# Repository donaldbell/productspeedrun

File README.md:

# Product Speedrun

**Product Speedrun** is a show about racing a randomly rolled product idea to a showcase-ready concept: an enclosure design, a circuit board and a product page. Everything the show designs is open, and this repository holds it.

**See the products:** https://donaldbell.github.io/productspeedrun/

Every product here is a **design proposal**, not something you can buy. Nothing has been manufactured, and each page lists what we still don't know.

## What's here

```
episodes/<NNN-slug>/        one folder per episode (Rev A, as aired)
  2-concept/, 3-layout/     concept art and control drawings
  4-model/                  the enclosure: model.step, model.stl, model.glb, notes
  5-electronics/            the circuit board: KiCad project, bom.csv, schematic and board renders, notes
  6-showcase/               the product page
products/<product>/rev-b/   later revisions of products we kept building, including firmware (7-firmware/)
tools/kicad/footprints/     custom footprints the KiCad projects use
tools/kicad/models/         3D models of parts the KiCad projects use
kit/                        the shared look of the product pages
```

## Using the designs

- **Enclosures:** open `4-model/model.step` in any CAD program, or print from `model.stl`. `build_model.py` and `model.solidcraft` are kept as a record of how the model was made; edit the STEP file.
- **Circuit boards:** open the `.kicad_pro` in [KiCad](https://www.kicad.org/) (the version each board was saved with is on its page). Keep the repository's folder layout so the custom footprints and 3D models in `tools/kicad/` are found. `src/design.py` and `src/layout.py` record the parts, nets and placement the board was generated from; edit the KiCad files.
- **Firmware:** PlatformIO projects in `products/<product>/rev-*/7-firmware/`.
- Each product page has a **Build on it** section with direct downloads and a prompt that hands the project to an AI coding agent.

## Licence and credit

Hardware is under CERN-OHL-P v2, writing and images under CC BY 4.0, and code under MIT. Details are in [LICENSE](LICENSE), the full texts in [LICENSES/](LICENSES/), and who made each episode in [CREDITS.md](CREDITS.md).

Credit line for reuse: *Based on Product Speedrun episode NNN by Donald Bell and &lt;guest&gt;, https://donaldbell.github.io/productspeedrun/*

The name "Product Speedrun" and its logo aren't covered by these licences.

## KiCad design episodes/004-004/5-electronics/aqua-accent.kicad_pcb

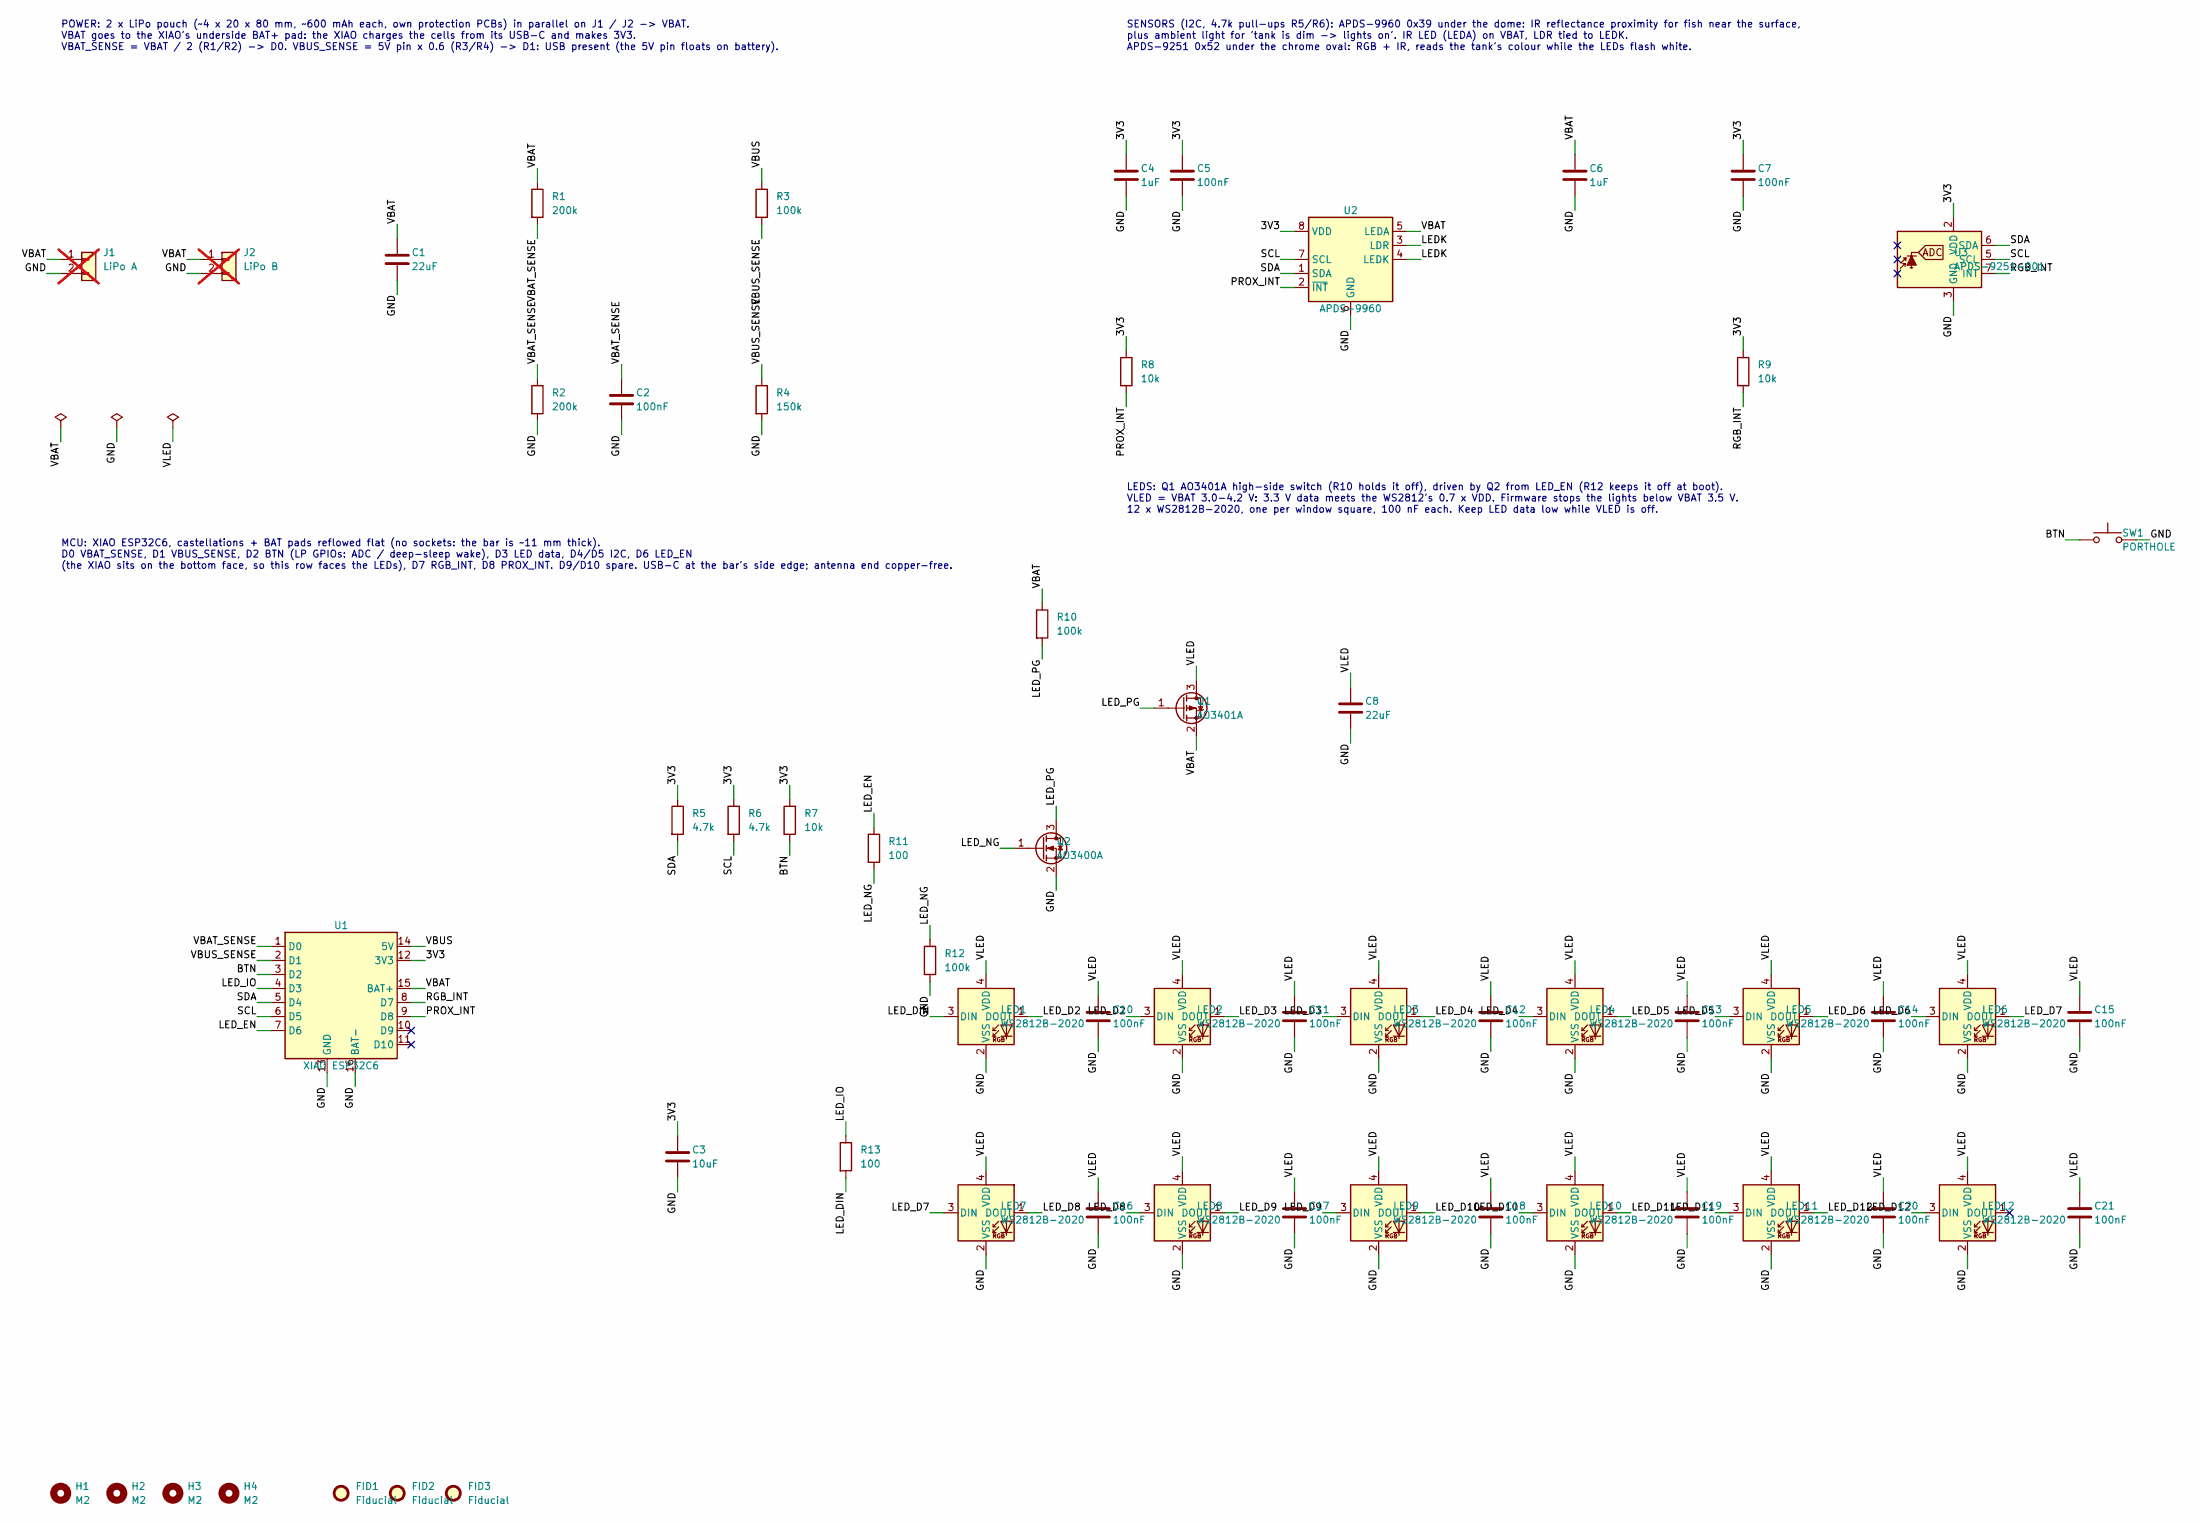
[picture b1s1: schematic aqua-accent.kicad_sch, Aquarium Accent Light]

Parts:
C1, C8: 22uF; C_0805_2012Metric; MPN CL21A226MAQNNNE; LCSC C45783
C2, C5, C7, C10, C11, C12, C13, C14, C15, C16, C17, C18, C19, C20, C21: 100nF; C_0603_1608Metric; MPN CC0603KRX7R9BB104; LCSC C14663
C3: 10uF; C_0805_2012Metric; MPN CL21A106KAYNNNE; LCSC C15850
C4, C6: 1uF; C_0603_1608Metric; MPN CL10A105KB8NNNC; LCSC C15849
FID1, FID2, FID3: Fiducial; Fiducial_1mm_Mask2mm
H1, H2, H3, H4: M2; MountingHole_2.2mm_M2
J1: LiPo A; SolderWire-0.1sqmm_1x02_P3.6mm_D0.4mm_OD1mm; not fitted
J2: LiPo B; SolderWire-0.1sqmm_1x02_P3.6mm_D0.4mm_OD1mm; not fitted
LED1, LED2, LED3, LED4, LED5, LED6, LED7, LED8, LED9, LED10, LED11, LED12: WS2812B-2020; LED_WS2812B-2020_PLCC4_2.0x2.0mm; MPN WS2812B-2020; LCSC C965555
Q1: AO3401A; SOT-23; MPN AO3401A; LCSC C15127
Q2: AO3400A; SOT-23; MPN AO3400A; LCSC C20917
R1, R2: 200k; R_0603_1608Metric; MPN 0603WAF2003T5E; LCSC C25811
R3, R10, R12: 100k; R_0603_1608Metric; MPN 0603WAF1003T5E; LCSC C25803
R4: 150k; R_0603_1608Metric; MPN 0603WAF1503T5E; LCSC C22807
R5, R6: 4.7k; R_0603_1608Metric; MPN 0603WAF4701T5E; LCSC C23162
R7, R8, R9: 10k; R_0603_1608Metric; MPN 0603WAF1002T5E; LCSC C25804
R11, R13: 100; R_0603_1608Metric; MPN 0603WAF1000T5E; LCSC C22775
SW1: PORTHOLE; SW_SPST_PTS810; MPN PTS810 SJM 250 SMTR LFS
U1: XIAO ESP32C6; Seeed_XIAO_ESP32C6_SMD; MPN 113991254
U2: APDS-9960; Avago_APDS-9960; MPN APDS-9960
U3: APDS-9251-001; Broadcom_LGA-8_2x2mm_P0.5mm; MPN APDS-9251-001

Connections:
/3V3: C3.1, C4.1, C5.1, C7.1, R5.1, R6.1, R7.1, R8.1, R9.1, U1.12 (3V3), U2.8 (VDD), U3.2 (VDD)
/BTN: R7.2, SW1.1, U1.3 (D2)
/GND: C1.2, C2.2, C3.2, C4.2, C5.2, C6.2, C7.2, C8.2, C10.2, C11.2, C12.2, C13.2, C14.2, C15.2, C16.2, C17.2, C18.2, C19.2, C20.2, C21.2, J1.2, J2.2, LED1.2 (VSS), LED2.2 (VSS), LED3.2 (VSS), LED4.2 (VSS), LED5.2 (VSS), LED6.2 (VSS), LED7.2 (VSS), LED8.2 (VSS), LED9.2 (VSS), LED10.2 (VSS), LED11.2 (VSS), LED12.2 (VSS), Q2.2 (S), R2.2, R4.2, R12.2, SW1.2, U1.13 (GND), U1.16 (BAT-), U2.6 (GND), U3.3 (GND)
/LEDK: U2.3 (LDR), U2.4 (LEDK)
/LED_D2: LED1.1 (DOUT), LED2.3 (DIN)
/LED_D3: LED2.1 (DOUT), LED3.3 (DIN)
/LED_D4: LED3.1 (DOUT), LED4.3 (DIN)
/LED_D5: LED4.1 (DOUT), LED5.3 (DIN)
/LED_D6: LED5.1 (DOUT), LED6.3 (DIN)
/LED_D7: LED6.1 (DOUT), LED7.3 (DIN)
/LED_D8: LED7.1 (DOUT), LED8.3 (DIN)
/LED_D9: LED8.1 (DOUT), LED9.3 (DIN)
/LED_D10: LED9.1 (DOUT), LED10.3 (DIN)
/LED_D11: LED10.1 (DOUT), LED11.3 (DIN)
/LED_D12: LED11.1 (DOUT), LED12.3 (DIN)
/LED_DIN: LED1.3 (DIN), R13.2
/LED_EN: R11.1, U1.7 (D6)
/LED_IO: R13.1, U1.4 (D3)
/LED_NG: Q2.1 (G), R11.2, R12.1
/LED_PG: Q1.1 (G), Q2.3 (D), R10.2
/PROX_INT: R8.2, U1.9 (D8), U2.2 (~INT)
/RGB_INT: R9.2, U1.8 (D7), U3.7 (INT)
/SCL: R6.2, U1.6 (D5), U2.7 (SCL), U3.5 (SCL)
/SDA: R5.2, U1.5 (D4), U2.1 (SDA), U3.6 (SDA)
/VBAT: C1.1, C6.1, J1.1, J2.1, Q1.2 (S), R1.1, R10.1, U1.15 (BAT+), U2.5 (LEDA)
/VBAT_SENSE: C2.1, R1.2, R2.1, U1.1 (D0)
/VBUS: R3.1, U1.14 (5V)
/VBUS_SENSE: R3.2, R4.1, U1.2 (D1)
/VLED: C8.1, C10.1, C11.1, C12.1, C13.1, C14.1, C15.1, C16.1, C17.1, C18.1, C19.1, C20.1, C21.1, LED1.4 (VDD), LED2.4 (VDD), LED3.4 (VDD), LED4.4 (VDD), LED5.4 (VDD), LED6.4 (VDD), LED7.4 (VDD), LED8.4 (VDD), LED9.4 (VDD), LED10.4 (VDD), LED11.4 (VDD), LED12.4 (VDD), Q1.3 (D)

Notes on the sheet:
POWER: 2 x LiPo pouch (~4 x 20 x 80 mm, ~600 mAh each, own protection PCBs) in parallel on J1 / J2 -> VBAT. VBAT goes to the XIAO's underside BAT+ pad: the XIAO charges the cells from its USB-C and makes 3V3. VBAT_SENSE = VBAT / 2 (R1/R2) -> D0. VBUS_SENSE = 5V pin x 0.6 (R3/R4) -> D1: USB present 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
MCU: XIAO ESP32C6, castellations + BAT pads reflowed flat (no sockets: the bar is ~11 mm thick). D0 VBAT_SENSE, D1 VBUS_SENSE, D2 BTN (LP GPIOs: ADC / deep-sleep wake), D3 LED data, D4/D5 I2C, D6 LED_EN (the XIAO sits on the bottom face, so this row faces the LEDs), D7 RGB_INT, D8 PROX_INT. D9/D10 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
SENSORS (I2C, 4.7k pull-ups R5/R6): APDS-9960 0x39 under the dome: IR reflectance proximity for fish near the surface, plus ambient light for 'tank is dim -> lights on'. IR LED (LEDA) on VBAT, LDR tied to LEDK. APDS-9251 0x52 under the chrome oval: RGB + IR, reads the tank's colour while the LEDs f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
LEDS: Q1 AO3401A high-side switch (R10 holds it off), driven by Q2 from LED_EN (R12 keeps it off at boot). VLED = VBAT 3.0-4.2 V: 3.3 V data meets the WS2812's 0.7 x VDD. Firmware stops the lights below VBAT 3.5 V. 12 x WS2812B-2020, one per window square, 100 nF each. Keep LED data low while VLED 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

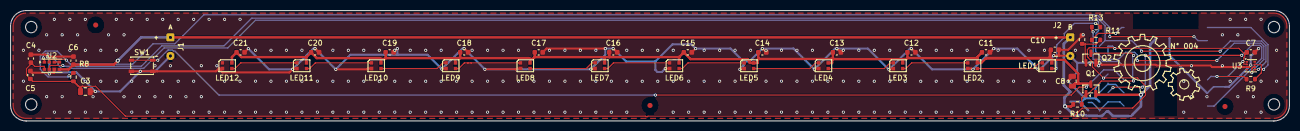
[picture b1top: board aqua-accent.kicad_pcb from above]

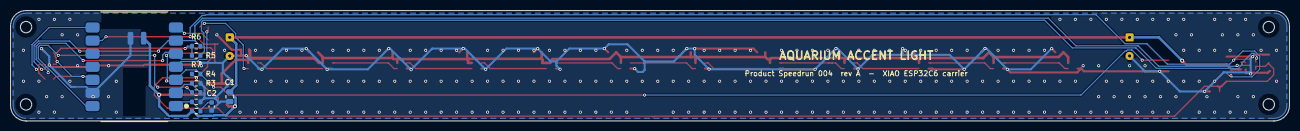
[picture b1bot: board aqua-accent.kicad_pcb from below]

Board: 2 copper layers, 248.0 x 21.4 mm, 60 parts (10 on the bottom side), 29 nets.

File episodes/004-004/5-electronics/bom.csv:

Ref,Qty,Value,Description,Footprint,MPN
C1 C8,2,22uF,"Capacitor, ceramic, 22 uF 25 V X5R 0805",C_0805_2012Metric,CL21A226MAQNNNE
C2 C5 C7 C10 C11 C12 C13 C14 C15 C16 C17 C18 C19 C20 C21,15,100nF,"Capacitor, ceramic, 100 nF 50 V X7R 0603",C_0603_1608Metric,CC0603KRX7R9BB104
C3,1,10uF,"Capacitor, ceramic, 10 uF 25 V X5R 0805",C_0805_2012Metric,CL21A106KAYNNNE
C4 C6,2,1uF,"Capacitor, ceramic, 1 uF 50 V X5R 0603",C_0603_1608Metric,CL10A105KB8NNNC
LED1 LED2 LED3 LED4 LED5 LED6 LED7 LED8 LED9 LED10 LED11 LED12,12,WS2812B-2020,"RGB LED 2 x 2 mm, one under each of the 12 window squares",LED_WS2812B-2020_PLCC4_2.0x2.0mm,WS2812B-2020
Q1,1,AO3401A,P-MOSFET -30 V -4 A SOT-23: high-side switch for the LED chain,SOT-23,AO3401A
Q2,1,AO3400A,N-MOSFET 30 V 5.7 A SOT-23: drives Q1's gate from the 3.3 V GPIO,SOT-23,AO3400A
R1 R2,2,200k,"Resistor, 1 %, 0603, 200k",R_0603_1608Metric,0603WAF2003T5E
R3 R10 R12,3,100k,"Resistor, 1 %, 0603, 100k",R_0603_1608Metric,0603WAF1003T5E
R4,1,150k,"Resistor, 1 %, 0603, 150k",R_0603_1608Metric,0603WAF1503T5E
R5 R6,2,4.7k,"Resistor, 1 %, 0603, 4.7k",R_0603_1608Metric,0603WAF4701T5E
R7 R8 R9,3,10k,"Resistor, 1 %, 0603, 10k",R_0603_1608Metric,0603WAF1002T5E
R11 R13,2,100,"Resistor, 1 %, 0603, 100",R_0603_1608Metric,0603WAF1000T5E
SW1,1,PORTHOLE,"Tact switch 4.2 x 3.2 x 2.5 mm SMD under the porthole boss: wake, mode, hold = open the control panel",SW_SPST_PTS810,PTS810 SJM 250 SMTR LFS
U1,1,XIAO ESP32C6,"Seeed XIAO ESP32C6 (USB-C, LiPo charger, 3.3 V LDO, ceramic antenna), castellations + BAT pads reflowed to the carrier",Seeed_XIAO_ESP32C6_SMD,113991254
U2,1,APDS-9960,"Proximity / gesture / ambient / RGBC sensor with IR LED, I2C 0x39: fish near the surface, room light",Avago_APDS-9960,APDS-9960
U3,1,APDS-9251-001,"Digital RGB + IR light sensor, I2C 0x52: reads the tank's colour",Broadcom_LGA-8_2x2mm_P0.5mm,APDS-9251-001
BT1,1,LiPo ~600 mAh,"LiPo pouch 3.7 V ~600 mAh, ~4 x 20 x 80 mm, with protection PCB, leads soldered to J1",off-board,generic 402080
BT2,1,LiPo ~600 mAh,"Second, matching cell in parallel, leads soldered to J2 (charge both to the same voltage before joining)",off-board,generic 402080

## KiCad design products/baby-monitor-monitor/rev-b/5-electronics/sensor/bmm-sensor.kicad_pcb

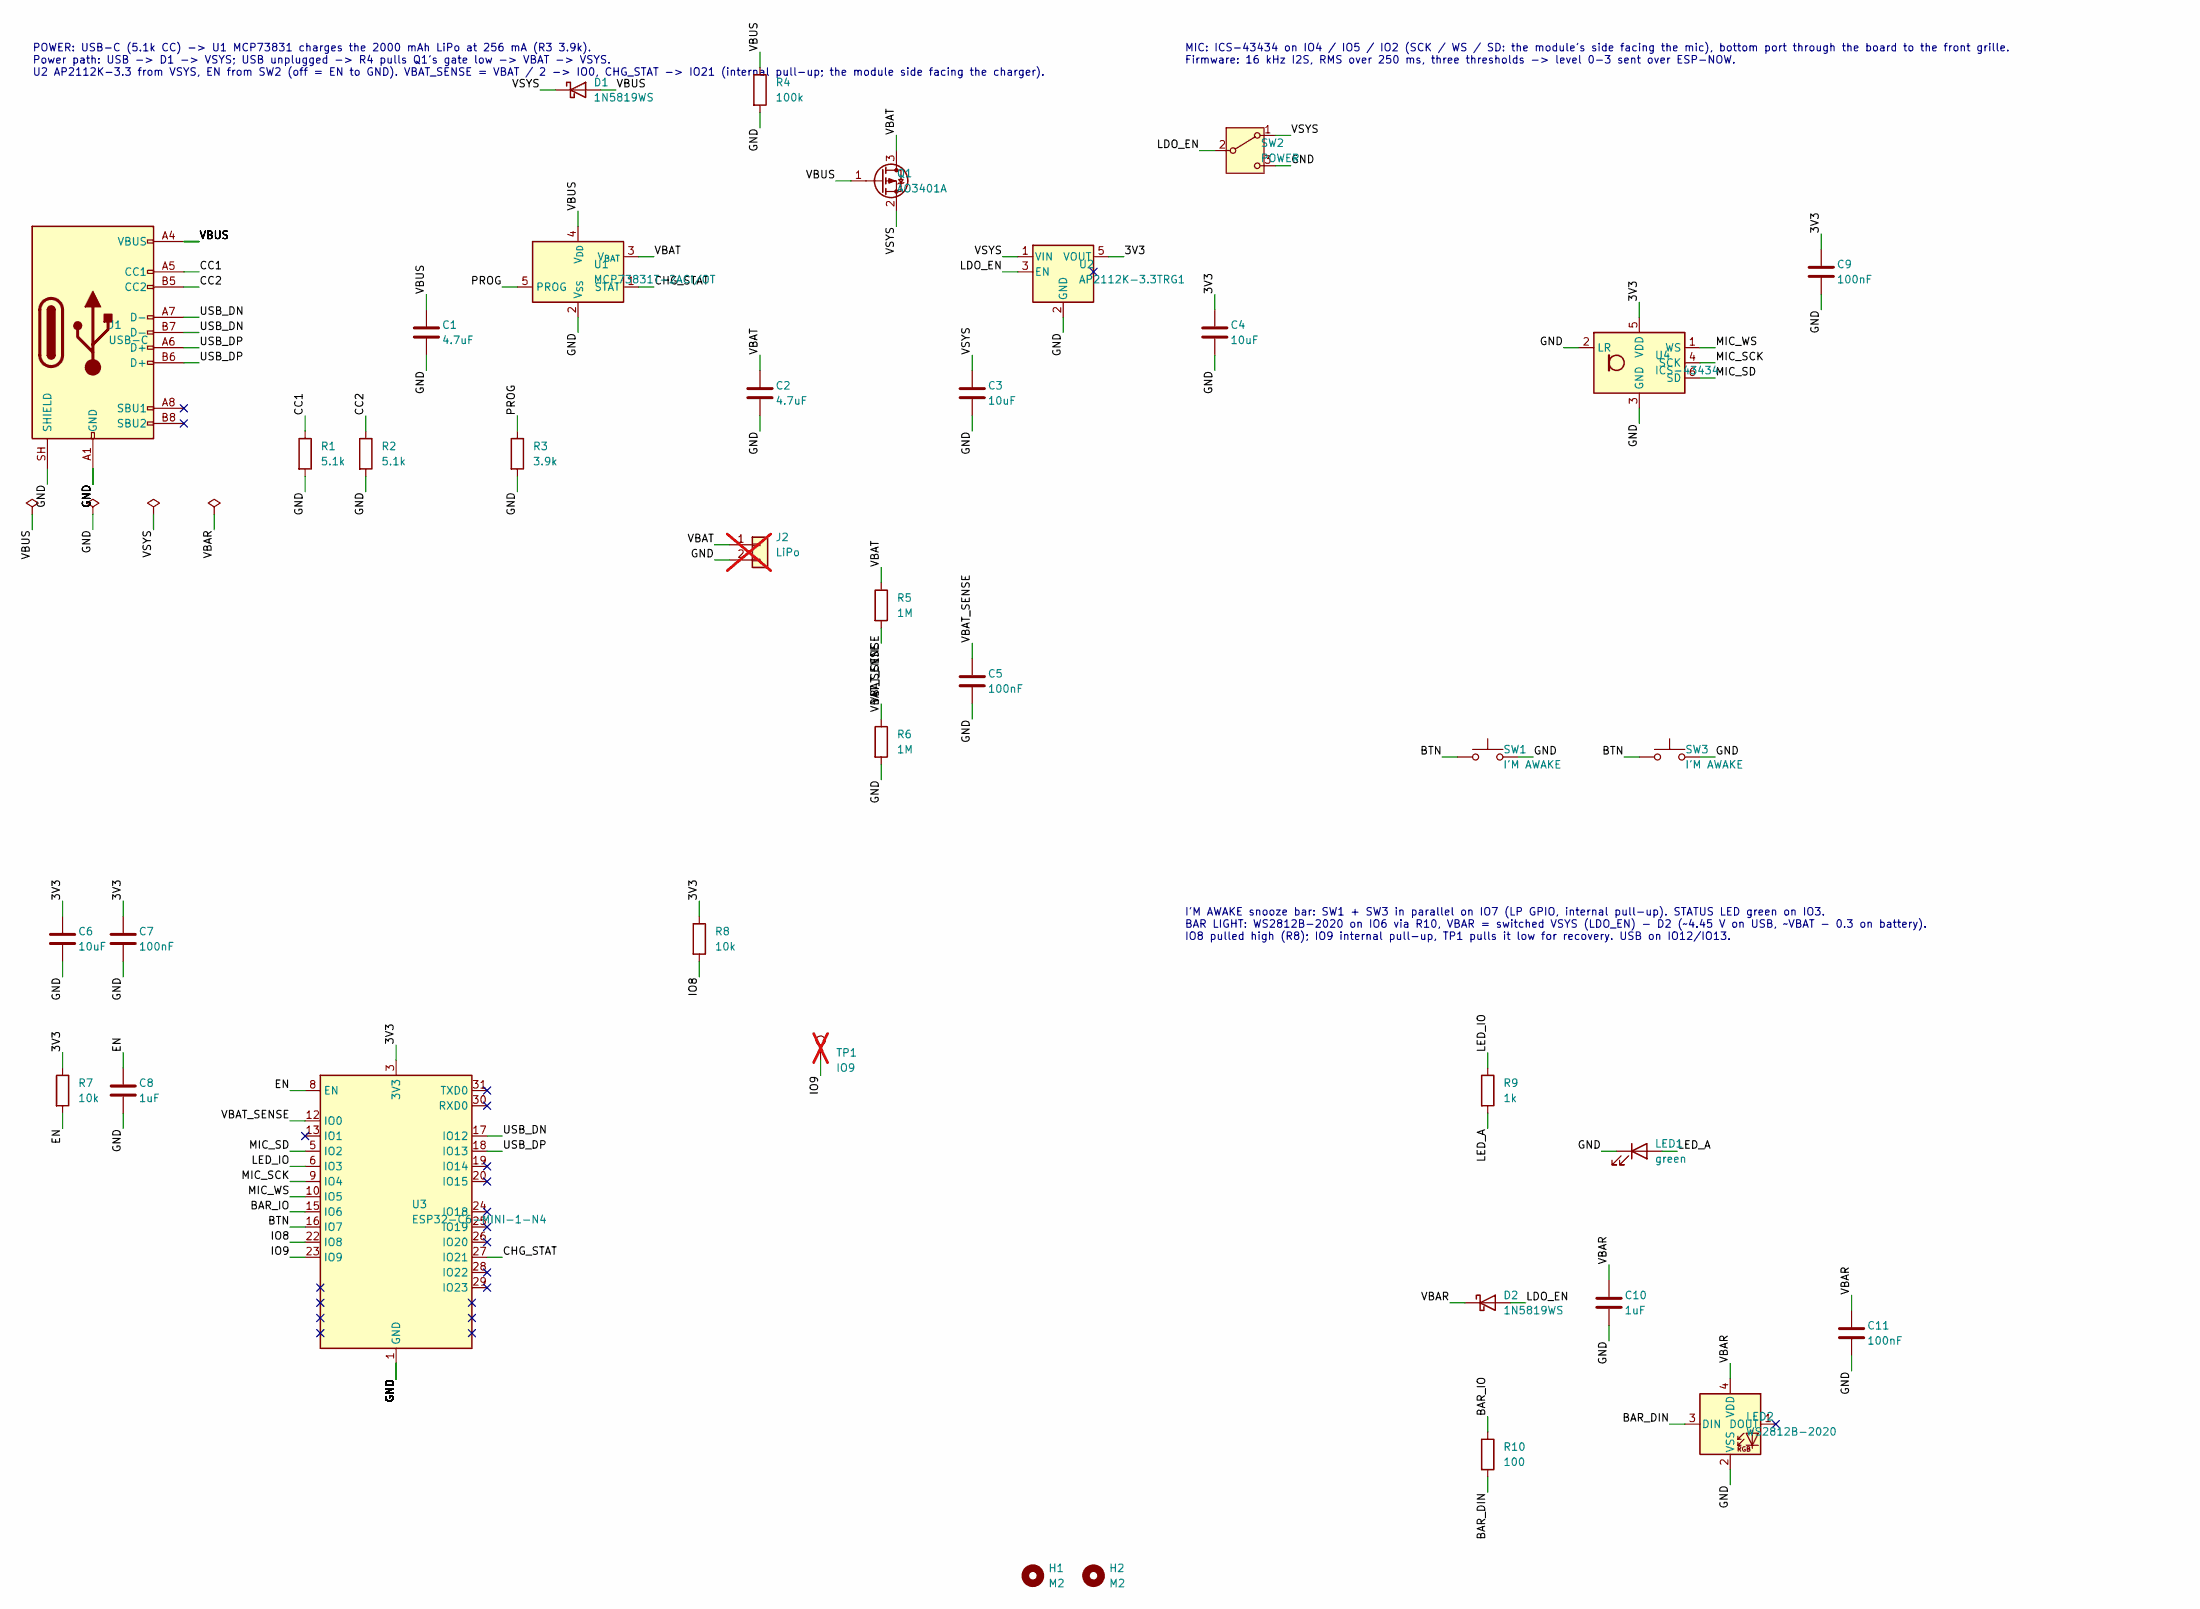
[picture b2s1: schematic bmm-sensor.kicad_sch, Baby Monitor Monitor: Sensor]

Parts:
C1, C2: 4.7uF; C_0603_1608Metric; MPN CL10A475KO8NNNC; LCSC C19666
C3, C4, C6: 10uF; C_0805_2012Metric; MPN CL21A106KAYNNNE; LCSC C15850
C5, C7, C9, C11: 100nF; C_0603_1608Metric; MPN CC0603KRX7R9BB104; LCSC C14663
C8, C10: 1uF; C_0603_1608Metric; MPN CL10A105KB8NNNC; LCSC C15849
D1, D2: 1N5819WS; D_SOD-323; MPN 1N5819WS; LCSC C191023
H1, H2: M2; MountingHole_2.2mm_M2
J1: USB-C; USB_C_Receptacle_GCT_USB4105-xx-A_16P_TopMnt_Horizontal; MPN USB4105-GF-A
J2: LiPo; SolderWire-0.1sqmm_1x02_P3.6mm_D0.4mm_OD1mm; not fitted
LED1: green; LED_0603_1608Metric; MPN KT-0603G; LCSC C72043
LED2: WS2812B-2020; LED_WS2812B-2020_PLCC4_2.0x2.0mm; MPN WS2812B-2020; LCSC C965555
Q1: AO3401A; SOT-23; MPN AO3401A; LCSC C15127
R1, R2: 5.1k; R_0603_1608Metric; MPN 0603WAF5101T5E; LCSC C23186
R3: 3.9k; R_0603_1608Metric; MPN 0603WAF3901T5E; LCSC C23018
R4: 100k; R_0603_1608Metric; MPN 0603WAF1003T5E; LCSC C25803
R5, R6: 1M; R_0603_1608Metric; MPN 0603WAF1004T5E; LCSC C22935
R7, R8: 10k; R_0603_1608Metric; MPN 0603WAF1002T5E; LCSC C25804
R9: 1k; R_0603_1608Metric; MPN 0603WAF1001T5E; LCSC C21190
R10: 100; R_0603_1608Metric; MPN 0603WAF1000T5E; LCSC C22775
SW1, SW3: I'M AWAKE; SW_Push_1TS009xxxx-xxxx-xxxx_6x6x5mm; MPN 1TS009A-1800-5000-CT
SW2: POWER; SW_SPDT_PCM12; MPN PCM12SMTR
TP1: IO9; TestPoint_Pad_D1.0mm; not fitted
U1: MCP73831T-2ACI/OT; SOT-23-5; MPN MCP73831T-2ACI/OT; LCSC C424093
U2: AP2112K-3.3TRG1; SOT-23-5; MPN AP2112K-3.3TRG1; LCSC C51118
U3: ESP32-C6-MINI-1-N4; ESP32-C6-MINI-1; MPN ESP32-C6-MINI-1-N4
U4: ICS-43434; InvenSense_ICS-43434-6_3.5x2.65mm; MPN ICS-43434

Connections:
/3V3: C4.1, C6.1, C7.1, C9.1, R7.1, R8.1, U2.5 (VOUT), U3.3 (3V3), U4.5 (VDD)
/BAR_DIN: LED2.3 (DIN), R10.2
/BAR_IO: R10.1, U3.15 (IO6)
/BTN: SW1.1, SW3.1, U3.16 (IO7)
/CC1: J1.A5 (CC1), R1.1
/CC2: J1.B5 (CC2), R2.1
/CHG_STAT: U1.1 (STAT), U3.27 (IO21)
/EN: C8.1, R7.2, U3.8 (EN)
/GND: C1.2, C2.2, C3.2, C4.2, C5.2, C6.2, C7.2, C8.2, C9.2, C10.2, C11.2, J1.A1 (GND), J1.A12 (GND), J1.B1 (GND), J1.B12 (GND), J1.SH (SHIELD), J2.2, LED1.1 (K), LED2.2 (VSS), R1.2, R2.2, R3.2, R4.2, R6.2, SW1.2, SW2.3 (C), SW3.2, U1.2 (V_{SS}), U2.2 (GND), U3.1 (GND), U3.2 (GND), U3.11 (GND), U3.14 (GND), U3.36 (GND), U3.37 (GND), U3.38 (GND), U3.39 (GND), U3.40 (GND), U3.41 (GND), U3.42 (GND), U3.43 (GND), U3.44 (GND), U3.45 (GND), U3.46 (GND), U3.47 (GND), U3.48 (GND), U3.49 (GND), U3.50 (GND), U3.51 (GND), U3.52 (GND), U3.53 (GND), U4.2 (LR), U4.3 (GND)
/IO8: R8.2, U3.22 (IO8)
/IO9: TP1.1, U3.23 (IO9)
/LDO_EN: D2.2 (A), SW2.2 (B), U2.3 (EN)
/LED_A: LED1.2 (A), R9.2
/LED_IO: R9.1, U3.6 (IO3)
/MIC_SCK: U3.9 (IO4), U4.4 (SCK)
/MIC_SD: U3.5 (IO2), U4.6 (SD)
/MIC_WS: U3.10 (IO5), U4.1 (WS)
/PROG: R3.1, U1.5 (PROG)
/USB_DN: J1.A7 (D-), J1.B7 (D-), U3.17 (IO12)
/USB_DP: J1.A6 (D+), J1.B6 (D+), U3.18 (IO13)
/VBAR: C10.1, C11.1, D2.1 (K), LED2.4 (VDD)
/VBAT: C2.1, J2.1, Q1.3 (D), R5.1, U1.3 (V_{BAT})
/VBAT_SENSE: C5.1, R5.2, R6.1, U3.12 (IO0)
/VBUS: C1.1, D1.2 (A), J1.A4 (VBUS), J1.A9 (VBUS), J1.B4 (VBUS), J1.B9 (VBUS), Q1.1 (G), R4.1, U1.4 (V_{DD})
/VSYS: C3.1, D1.1 (K), Q1.2 (S), SW2.1 (A), U2.1 (VIN)

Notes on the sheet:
POWER: USB-C (5.1k CC) -> U1 MCP73831 charges the 2000 mAh LiPo at 256 mA (R3 3.9k). Power path: USB -> D1 -> VSYS; USB unplugged -> R4 pulls Q1's gate low -> VBAT -> VSYS. U2 AP2112K-3.3 from VSYS, EN from SW2 (off = EN to GND). VBAT_SENSE = VBAT / 2 -> IO0, CHG_STAT -> IO21 (internal pull-up; the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
MIC: ICS-43434 on IO4 / IO5 / IO2 (SCK / WS / SD: the module's side facing the mic), bottom port through the board to the front grille. Firmware: 16 kHz I2S, RMS over 250 ms, three thresholds -> level 0-3 sent over ESP-NOW.
I'M AWAKE snooze bar: SW1 + SW3 in parallel on IO7 (LP GPIO, internal pull-up). STATUS LED green on IO3. BAR LIGHT: WS2812B-2020 on IO6 via R10, VBAR = switched VSYS (LDO_EN) - D2 (~4.45 V on USB, ~VBAT - 0.3 on battery). IO8 pulled high (R8); IO9 internal pull-up, TP1 pulls it low for recovery. US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

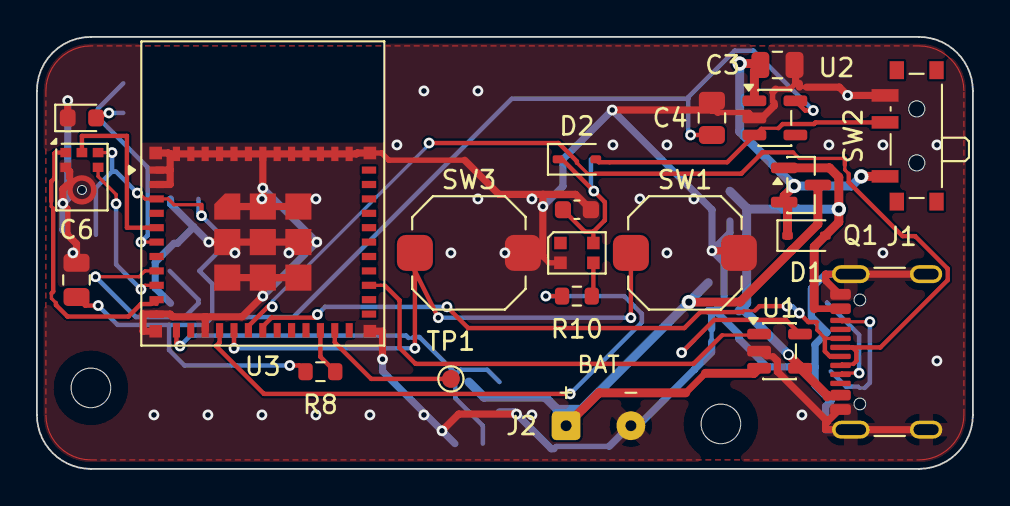
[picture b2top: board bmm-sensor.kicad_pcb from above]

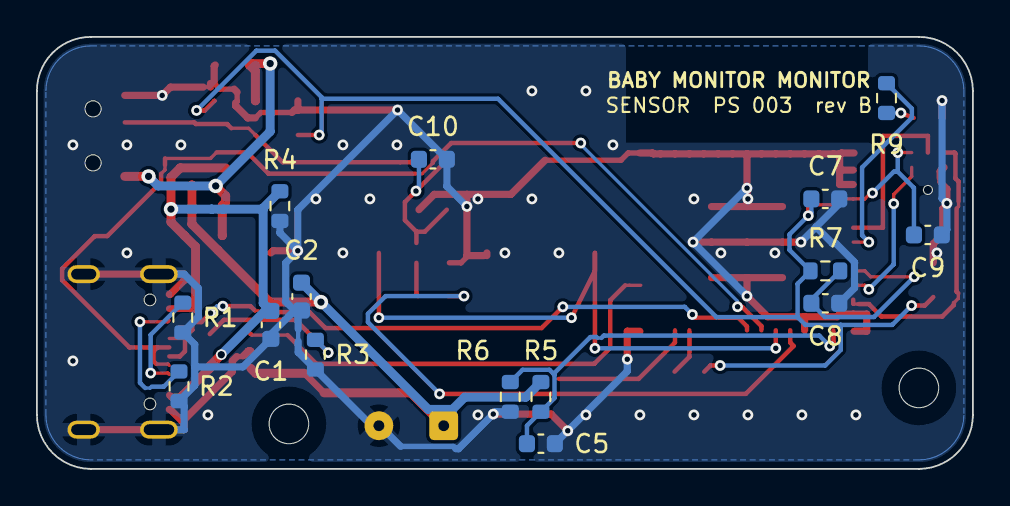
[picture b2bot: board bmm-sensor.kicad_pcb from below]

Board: 2 copper layers, 52.0 x 24.0 mm, 38 parts (15 on the bottom side), 25 nets.

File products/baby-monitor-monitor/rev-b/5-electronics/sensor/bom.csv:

Ref,Qty,Value,Description,Footprint,MPN
C1 C2,2,4.7uF,"Capacitor, ceramic, 4.7 uF 16 V X5R 0603",C_0603_1608Metric,CL10A475KO8NNNC
C3 C4 C6,3,10uF,"Capacitor, ceramic, 10 uF 25 V X5R 0805",C_0805_2012Metric,CL21A106KAYNNNE
C5 C7 C9 C11,4,100nF,"Capacitor, ceramic, 100 nF 50 V X7R 0603",C_0603_1608Metric,CC0603KRX7R9BB104
C8 C10,2,1uF,"Capacitor, ceramic, 1 uF 50 V X5R 0603",C_0603_1608Metric,CL10A105KB8NNNC
D1 D2,2,1N5819WS,Schottky 40 V 1 A SOD-323: USB into the system rail,D_SOD-323,1N5819WS
J1,1,USB-C,"USB-C receptacle, USB 2.0, 16 pin, top mount: power, charging and flashing (ESP32-C6 native USB)",USB_C_Receptacle_GCT_USB4105-xx-A_16P_TopMnt_Horizontal,USB4105-GF-A
LED1,1,green,LED green 0603: status under the front light pipe,LED_0603_1608Metric,KT-0603G
LED2,1,WS2812B-2020,RGB LED 2 x 2 mm under the clear snooze bar: location in the dark + state,LED_WS2812B-2020_PLCC4_2.0x2.0mm,WS2812B-2020
Q1,1,AO3401A,P-MOSFET -30 V -4 A SOT-23: battery into the system rail when USB is absent,SOT-23,AO3401A
R1 R2,2,5.1k,"Resistor, 1 %, 0603, 5.1k",R_0603_1608Metric,0603WAF5101T5E
R3,1,3.9k,"Resistor, 1 %, 0603, 3.9k",R_0603_1608Metric,0603WAF3901T5E
R4,1,100k,"Resistor, 1 %, 0603, 100k",R_0603_1608Metric,0603WAF1003T5E
R5 R6,2,1M,"Resistor, 1 %, 0603, 1M",R_0603_1608Metric,0603WAF1004T5E
R7 R8,2,10k,"Resistor, 1 %, 0603, 10k",R_0603_1608Metric,0603WAF1002T5E
R9,1,1k,"Resistor, 1 %, 0603, 1k",R_0603_1608Metric,0603WAF1001T5E
R10,1,100,"Resistor, 1 %, 0603, 100",R_0603_1608Metric,0603WAF1000T5E
SW1 SW3,2,I'M AWAKE,"Tact switch 6 x 6 x 5 mm SMD under the snooze bar's back end: tap = I'm awake, hold = test / pair",SW_Push_1TS009xxxx-xxxx-xxxx_6x6x5mm,1TS009A-1800-5000-CT
SW2,1,POWER,"Slide switch SPDT right-angle SMD (C&K PCM12): on = LDO enabled, off = EN to GND",SW_SPDT_PCM12,PCM12SMTR
U1,1,MCP73831T-2ACI/OT,"Li-ion/LiPo linear charger 4.2 V, SOT-23-5",SOT-23-5,MCP73831T-2ACI/OT
U2,1,AP2112K-3.3TRG1,"LDO 3.3 V 600 mA, SOT-23-5, enabled by the power switch",SOT-23-5,AP2112K-3.3TRG1
U3,1,ESP32-C6-MINI-1-N4,"ESP32-C6 Wi-Fi 6 / BLE 5 / 802.15.4 module (ESP-NOW), 4 MB flash, PCB antenna, 13.2 x 16.6 x 2.4 mm",ESP32-C6-MINI-1,ESP32-C6-MINI-1-N4
U4,1,ICS-43434,"I2S MEMS microphone, bottom port over a 1 mm hole through the board, L/R low = left slot",InvenSense_ICS-43434-6_3.5x2.65mm,ICS-43434
BT1,1,LiPo 2000 mAh,"LiPo 3.7 V ~2000 mAh with protection PCB, 103450 (10 x 34 x 50 mm), leads soldered to J2",off-board,generic 103450

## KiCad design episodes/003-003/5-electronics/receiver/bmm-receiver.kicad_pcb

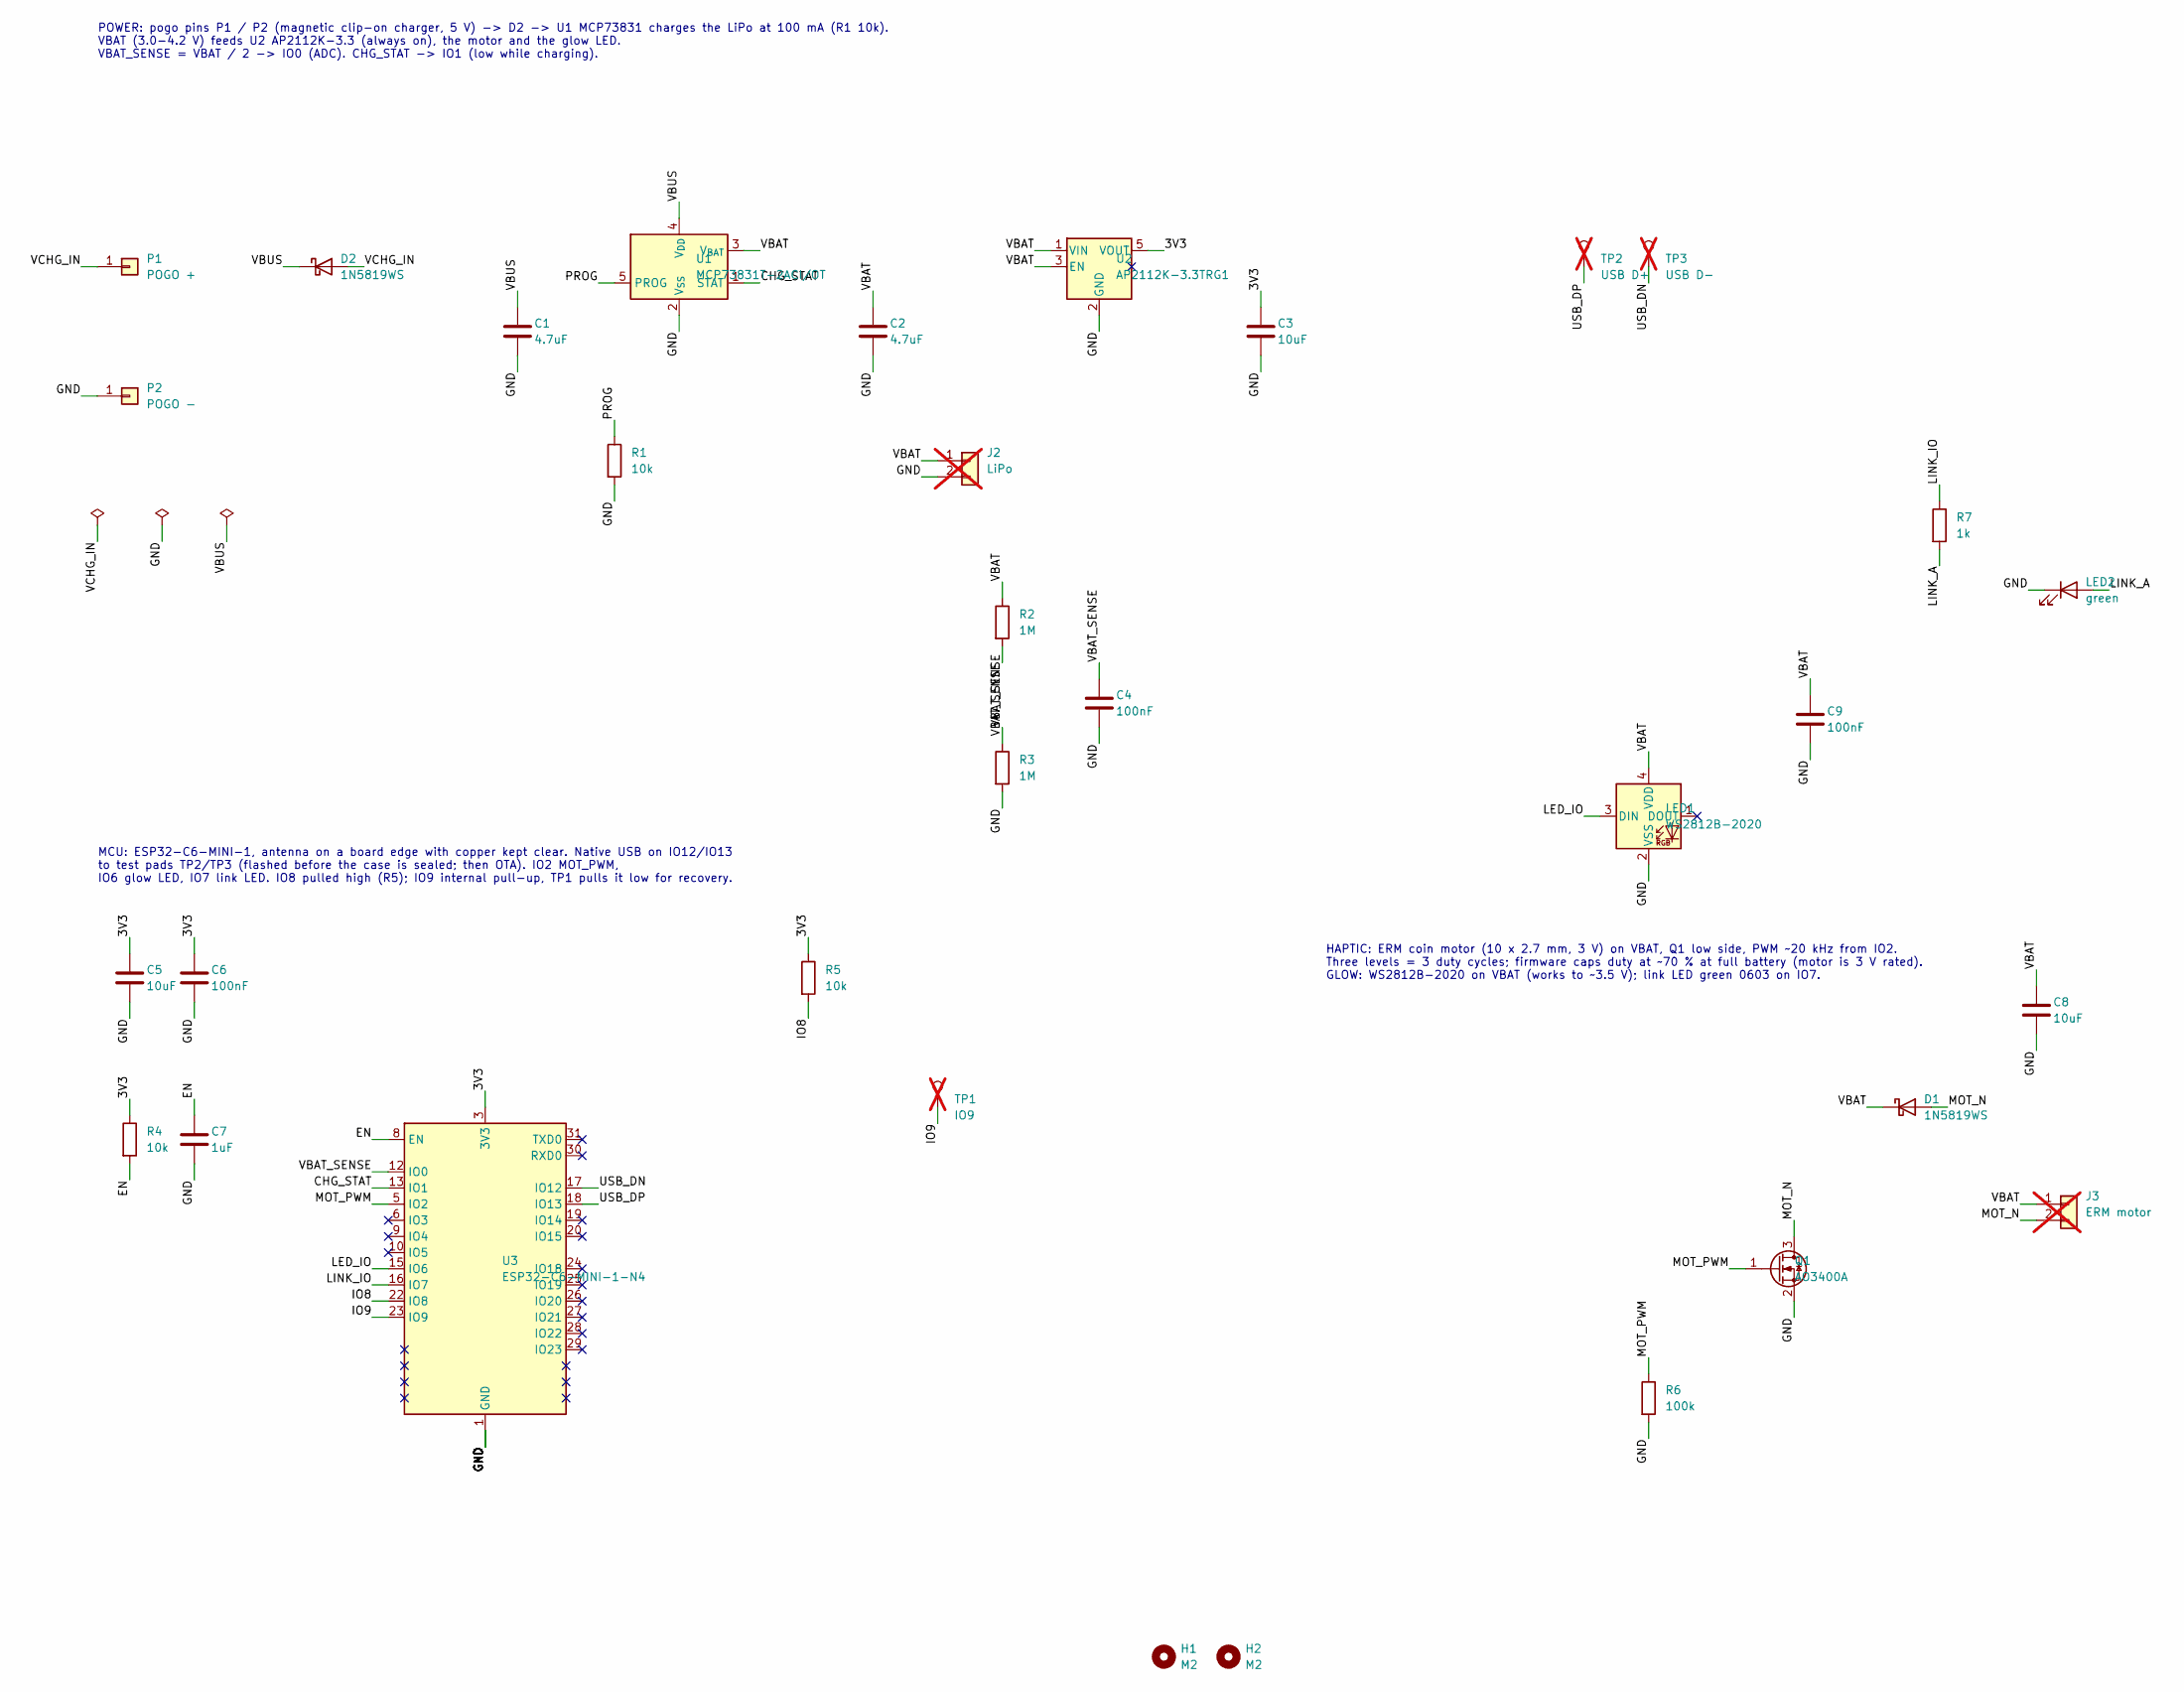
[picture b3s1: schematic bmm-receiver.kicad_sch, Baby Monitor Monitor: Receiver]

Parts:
C1, C2: 4.7uF; C_0603_1608Metric; MPN CL10A475KO8NNNC; LCSC C19666
C3, C5, C8: 10uF; C_0805_2012Metric; MPN CL21A106KAYNNNE; LCSC C15850
C4, C6, C9: 100nF; C_0603_1608Metric; MPN CC0603KRX7R9BB104; LCSC C14663
C7: 1uF; C_0603_1608Metric; MPN CL10A105KB8NNNC; LCSC C15849
D1, D2: 1N5819WS; D_SOD-323; MPN 1N5819WS; LCSC C191023
H1, H2: M2; MountingHole_2.2mm_M2
J2: LiPo; SolderWire-0.1sqmm_1x02_P3.6mm_D0.4mm_OD1mm; not fitted
J3: ERM motor; SolderWire-0.1sqmm_1x02_P3.6mm_D0.4mm_OD1mm; not fitted
LED1: WS2812B-2020; LED_WS2812B-2020_PLCC4_2.0x2.0mm; MPN WS2812B-2020; LCSC C965555
LED2: green; LED_0603_1608Metric; MPN KT-0603G; LCSC C72043
P1: POGO +; TestPoint_Pad_D2.0mm; MPN Mill-Max 0907 SMD spring pin (~5 mm)
P2: POGO -; TestPoint_Pad_D2.0mm; MPN Mill-Max 0907 SMD spring pin (~5 mm)
Q1: AO3400A; SOT-23; MPN AO3400A; LCSC C20917
R1, R4, R5: 10k; R_0603_1608Metric; MPN 0603WAF1002T5E; LCSC C25804
R2, R3: 1M; R_0603_1608Metric; MPN 0603WAF1004T5E; LCSC C22935
R6: 100k; R_0603_1608Metric; MPN 0603WAF1003T5E; LCSC C25803
R7: 1k; R_0603_1608Metric; MPN 0603WAF1001T5E; LCSC C21190
TP1: IO9; TestPoint_Pad_D1.0mm; not fitted
TP2: USB D+; TestPoint_Pad_D1.0mm; not fitted
TP3: USB D-; TestPoint_Pad_D1.0mm; not fitted
U1: MCP73831T-2ACI/OT; SOT-23-5; MPN MCP73831T-2ACI/OT; LCSC C424093
U2: AP2112K-3.3TRG1; SOT-23-5; MPN AP2112K-3.3TRG1; LCSC C51118
U3: ESP32-C6-MINI-1-N4; ESP32-C6-MINI-1; MPN ESP32-C6-MINI-1-N4

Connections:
/3V3: C3.1, C5.1, C6.1, R4.1, R5.1, U2.5 (VOUT), U3.3 (3V3)
/CHG_STAT: U1.1 (STAT), U3.13 (IO1)
/EN: C7.1, R4.2, U3.8 (EN)
/GND: C1.2, C2.2, C3.2, C4.2, C5.2, C6.2, C7.2, C8.2, C9.2, J2.2, LED1.2 (VSS), LED2.1 (K), P2.1, Q1.2 (S), R1.2, R3.2, R6.2, U1.2 (V_{SS}), U2.2 (GND), U3.1 (GND), U3.2 (GND), U3.11 (GND), U3.14 (GND), U3.36 (GND), U3.37 (GND), U3.38 (GND), U3.39 (GND), U3.40 (GND), U3.41 (GND), U3.42 (GND), U3.43 (GND), U3.44 (GND), U3.45 (GND), U3.46 (GND), U3.47 (GND), U3.48 (GND), U3.49 (GND), U3.50 (GND), U3.51 (GND), U3.52 (GND), U3.53 (GND)
/IO8: R5.2, U3.22 (IO8)
/IO9: TP1.1, U3.23 (IO9)
/LED_IO: LED1.3 (DIN), U3.15 (IO6)
/LINK_A: LED2.2 (A), R7.2
/LINK_IO: R7.1, U3.16 (IO7)
/MOT_N: D1.2 (A), J3.2, Q1.3 (D)
/MOT_PWM: Q1.1 (G), R6.1, U3.5 (IO2)
/PROG: R1.1, U1.5 (PROG)
/USB_DN: TP3.1, U3.17 (IO12)
/USB_DP: TP2.1, U3.18 (IO13)
/VBAT: C2.1, C8.1, C9.1, D1.1 (K), J2.1, J3.1, LED1.4 (VDD), R2.1, U1.3 (V_{BAT}), U2.1 (VIN), U2.3 (EN)
/VBAT_SENSE: C4.1, R2.2, R3.1, U3.12 (IO0)
/VBUS: C1.1, D2.1 (K), U1.4 (V_{DD})
/VCHG_IN: D2.2 (A), P1.1

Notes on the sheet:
POWER: pogo pins P1 / P2 (magnetic clip-on charger, 5 V) -> D2 -> U1 MCP73831 charges the LiPo at 100 mA (R1 10k). VBAT (3.0-4.2 V) feeds U2 AP2112K-3.3 (always on), the motor and the glow LED. VBAT_SENSE = VBAT / 2 -> IO0 (ADC). CHG_STAT -> IO1 (low while charging).
MCU: ESP32-C6-MINI-1, antenna on a board edge with copper kept clear. Native USB on IO12/IO13 to test pads TP2/TP3 (flashed before the case is sealed; then OTA). IO2 MOT_PWM, IO6 glow LED, IO7 link LED. IO8 pulled high (R5); IO9 internal pull-up, TP1 pulls it low for recovery.
HAPTIC: ERM coin motor (10 x 2.7 mm, 3 V) on VBAT, Q1 low side, PWM ~20 kHz from IO2. Three levels = 3 duty cycles; firmware caps duty at ~70 % at full battery (motor is 3 V rated). GLOW: WS2812B-2020 on VBAT (works to ~3.5 V); link LED green 0603 on IO7.

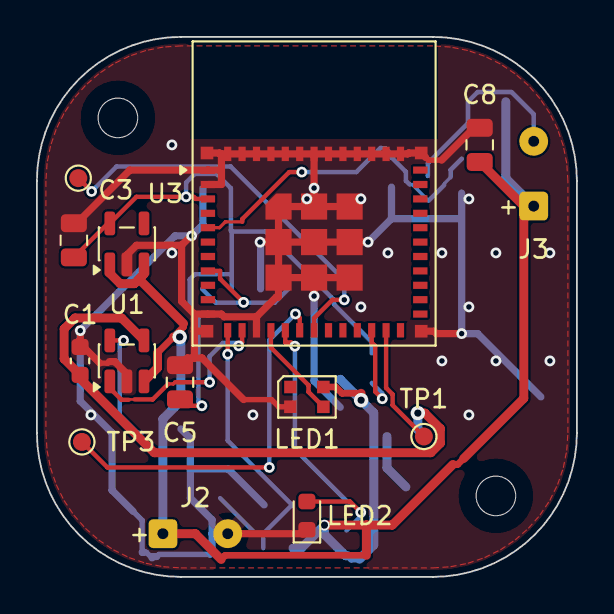
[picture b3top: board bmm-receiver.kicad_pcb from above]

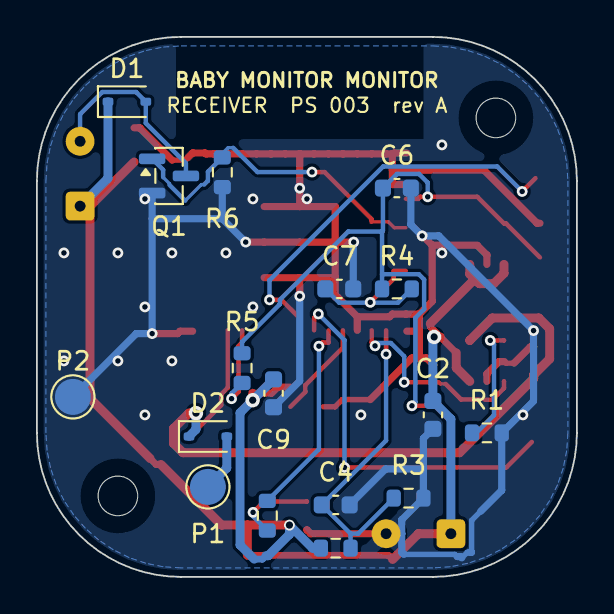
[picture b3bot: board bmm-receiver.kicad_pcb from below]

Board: 2 copper layers, 30.0 x 30.0 mm, 33 parts (17 on the bottom side), 18 nets.
